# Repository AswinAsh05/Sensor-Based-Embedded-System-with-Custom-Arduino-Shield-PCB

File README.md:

# Sensor-Based-Embedded-System-with-Custom-Arduino-Shield-PCB

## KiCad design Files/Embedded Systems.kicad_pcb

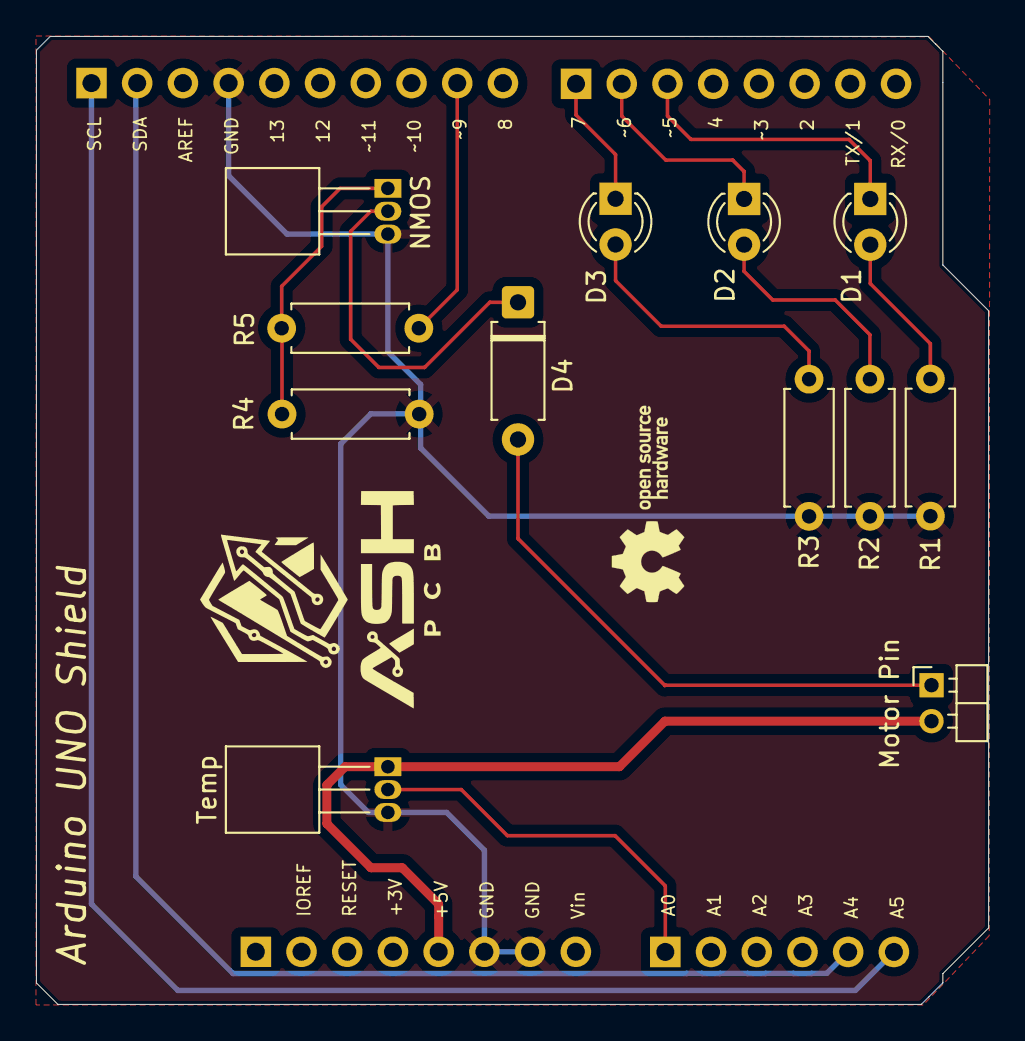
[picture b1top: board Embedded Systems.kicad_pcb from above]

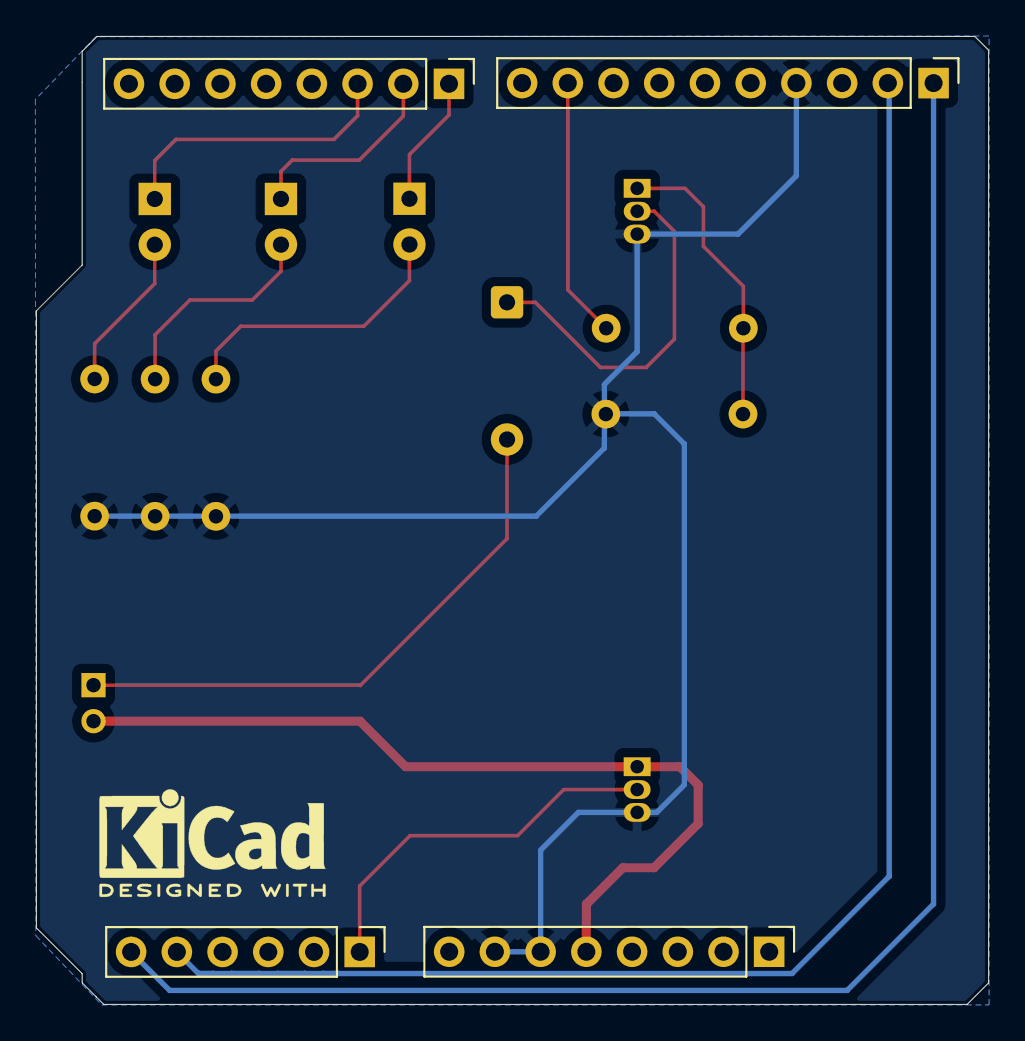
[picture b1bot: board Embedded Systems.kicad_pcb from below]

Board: 2 copper layers, 52.9 x 53.8 mm, 16 parts (4 on the bottom side), 15 nets.

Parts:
D1: RED; LED_D3.0mm_Clear
D2: YELLOW; LED_D3.0mm_Clear
D3: GREEN; LED_D3.0mm_Clear
D4: D; D_A-405_P7.62mm_Horizontal
J1: Power; PinHeader_1x08_P2.54mm_Vertical
J2: Digital/PWM; PinHeader_1x10_P2.54mm_Vertical
J3: Analog; PinHeader_1x06_P2.54mm_Vertical
J4: Digital/PWM; PinHeader_1x08_P2.54mm_Vertical
Motor Pin: Motor_DC; PinHeader_1x02_P2.00mm_Horizontal
NMOS: Q_NMOS; TO-92_Inline_Horizontal1
R1, R2, R3: 220Ω; R_Axial_DIN0207_L6.3mm_D2.5mm_P7.62mm_Horizontal
R4: 10k; R_Axial_DIN0207_L6.3mm_D2.5mm_P7.62mm_Horizontal
R5: 1k; R_Axial_DIN0207_L6.3mm_D2.5mm_P7.62mm_Horizontal
Temp: LM35-LP; TO-92_Inline_Horizontal1

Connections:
+5V: J1.5, Motor Pin.2 (-), Temp.1 (+V_{S})
/SCL/A5: J2.1, J3.6
/SDA/A4: J2.2, J3.5
GND: J1.6, J1.7, J2.4, NMOS.3, R1.2 (-), R2.2 (-), R3.2 (-), R4.2 (-), Temp.3 (GND)
GREEN: D3.1 (K), J4.1
MOTOR: J2.9, R5.1 (+)
unnamed: D1.2 (A), R1.1 (+)
unnamed: D2.2 (A), R2.1 (+)
unnamed: D3.2 (A), R3.1 (+)
unnamed: D4.2 (A), Motor Pin.1 (+)
unnamed: D4.1 (K), NMOS.2
unnamed: NMOS.1, R4.1 (+), R5.2 (-)
RED: D1.1 (K), J4.3
TEMP: J3.1, Temp.2 (V_{OUT})
YELLOW: D2.1 (K), J4.2

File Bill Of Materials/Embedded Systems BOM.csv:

Reference,Value,Datasheet,Footprint,Qty,DNP
J1,Power,,Connector_PinHeader_2.54mm:PinHeader_1x08_P2.54mm_Vertical,1,
"J2,J4",Digital/PWM,,"Connector_PinHeader_2.54mm:PinHeader_1x08_P2.54mm_Vertical,Connector_PinHeader_2.54mm:PinHeader_1x10_P2.54mm_Vertical",2,
J3,Analog,,Connector_PinHeader_2.54mm:PinHeader_1x06_P2.54mm_Vertical,1,
"R1,R2,R3",220Ω,,Resistor_THT:R_Axial_DIN0207_L6.3mm_D2.5mm_P7.62mm_Horizontal,3,
R4,10k,,Resistor_THT:R_Axial_DIN0207_L6.3mm_D2.5mm_P7.62mm_Horizontal,1,
R5,1k,,Resistor_THT:R_Axial_DIN0207_L6.3mm_D2.5mm_P7.62mm_Horizontal,1,
U1,LM35-LP,http://www.ti.com/lit/ds/symlink/lm35.pdf,Package_TO_SOT_THT:TO-92_Inline_Horizontal1,1,
D1,RED,~,LED_THT:LED_D3.0mm_Clear,1,
D2,YELLOW,~,LED_THT:LED_D3.0mm_Clear,1,
D3,GREEN,~,LED_THT:LED_D3.0mm_Clear,1,
D4,D,~,Diode_THT:D_A-405_P7.62mm_Horizontal,1,
M1,Motor_DC,~,Connector_PinHeader_2.00mm:PinHeader_1x02_P2.00mm_Horizontal,1,
Q1,Q_NMOS,~,Package_TO_SOT_THT:TO-92_Inline_Horizontal1,1,

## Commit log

2026-04-18 Create LICENSE
